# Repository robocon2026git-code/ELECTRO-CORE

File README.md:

\# GITHUB WORKFLOW GUIDE

Welcome to \*\*ROBOCON WORKSPACE\*\*

This document explains \*\*how team members should clone the repo, set up Git, and work using feature branches\*\*.

⚠️ Direct changes to `main` are NOT allowed.  

All work must be done using \*\*feature branches\*\* and merged via \*\*Pull Requests (PRs)\*\*.

---

\## 🧠 Git Basics (Quick Understanding)

\- \*\*Repository (repo)\*\* → Project stored with version control

\- \*\*main branch\*\* → Stable, reviewed code only

\- \*\*feature branch\*\* → Your personal workspace

\- \*\*commit\*\* → A saved snapshot of changes

\- \*\*origin\*\* → Remote GitHub repository

\- \*\*Pull Request (PR)\*\* → Request to merge code into `main`

---

\## One-Time Setup (Required on Every New PC)

Run these commands \*\*once\*\* after installing Git:

```bash

git config --global user.name "Your Name"

git config --global user.email "your-email@example.com"

git config --global init.defaultBranch main

\## To verify configuration

git config --global --list

**## Cloning and work steps starts from here:**

!!!!IMPORTANT ONE TIME SETTING AFTER INSTALLED GIT:

git clone https://github.com/robocon2026git-code/ELECTRICAL-AND-EMBEDDED.git

# \## REGULAR WORK PROCEDURE

1)cd ELECTRO-CORE

2)git status

3)git checkout main					//This line says go to main branch

4)git pull origin main					//Important step otherwise you might miss some files that was updated recently

5)git checkout -b feature/short-description		//Creating your local workspace

    ex:

        git checkout -b feature/pneumatic\_actuation

	git checkout -b feature/arduino-motor

	git checkout -b feature/i2c-driver

After work done run this command once

6)git status

\## THE FOLLOWING STEPS ARE AFTER COMPLETION OF YOUR WORK

\*\* THIS THREE COMMENTS WE WILL USE FREQUENTLY

7)git add .

8)git commit -m "Added new functionality to drive train"

Run this command only when your first push after creation of your feature branch

9) a_)git push -u origin feature/your-branch-name

from next push onwards you can just type

   b_)git push

For local space

10) a_)git branch -d feature/your-branch-name		//Run this comment only after code is merged. This will delete your branch

For remote space

    b_)git push origin --delete feature/your-branch-name

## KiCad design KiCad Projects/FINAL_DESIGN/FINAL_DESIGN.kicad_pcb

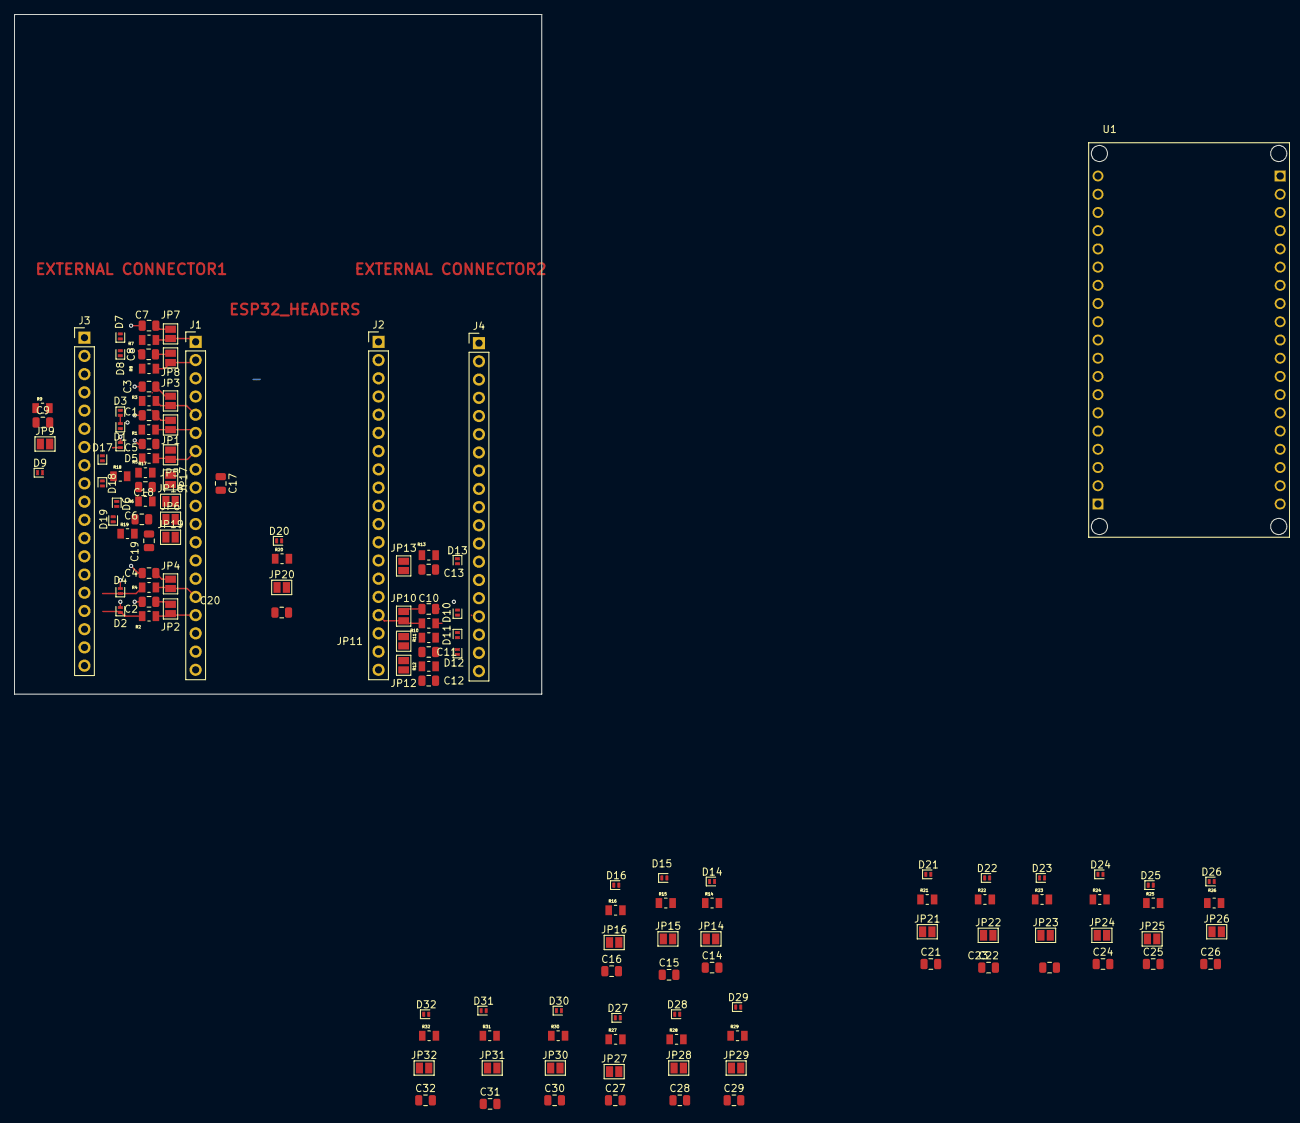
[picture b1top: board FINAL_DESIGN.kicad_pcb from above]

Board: 2 copper layers, 73.5 x 94.8 mm, 133 parts (0 on the bottom side), 100 nets.

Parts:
C1, C2, C3, C4, C5, C6, C7, C8, C9, C10, C11, C12, C13, C14, C15, C16, C17, C18, C19, C20, C21, C22, C23, C24, C25, C26, C27, C28, C29, C30, C31, C32: 100nf; C_0805_2012Metric
D1, D2, D3, D4, D5, D6, D7, D8, D9, D10, D11, D12, D13, D14, D15, D16, D17, D18, D19, D20, D21, D22, D23, D24, D25, D26, D27, D28, D29, D30, D31, D32: D_Zener; D_SOD-882
J1, J2, J3, J4: Conn_01x19_Socket; PinHeader_1x19_P2.54mm_Vertical
JP1, JP2, JP3, JP4, JP5, JP6, JP7, JP8, JP9, JP10, JP11, JP12, JP13, JP14, JP15, JP16, JP17, JP18, JP19, JP20, JP21, JP22, JP23, JP24, JP25, JP26, JP27, JP28, JP29, JP30, JP31, JP32: SolderJumper_2_Open; SolderJumper-2_P1.3mm_Open_Pad1.0x1.5mm
R1, R2, R3, R4, R5, R6, R7, R8, R9, R10, R11, R12, R13, R14, R15, R16, R17, R18, R19, R20, R21, R22, R23, R24, R25, R26, R27, R28, R29, R30, R31, R32: 150; RESC2012X60N
U1: ESP32_NODEMCU; MODULE_ESP32_NODEMCU

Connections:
+3V3: J2.1, J4.1
/CLK: D7.1 (K), J3.1, R7.1
/CMD: D12.1 (K), J4.18, R12.1
/EN: J2.2, J4.2
/IO16: JP17.2 (B), R17.2
/IO_0: J1.6, JP1.2 (B), R1.2
/IO_1: J1.16, JP2.2 (B), R2.2
/IO_2: J1.5, JP3.2 (B), R3.2
/IO_3: J1.15, JP4.2 (B), R4.2
/IO_4: J1.7, JP5.2 (B), R5.2
/IO_5: J1.10, JP6.2 (B), R6.2
/IO_6: J1.1, JP7.2 (B), R7.2
/IO_7: J1.2, JP8.2 (B), R8.2
/IO_8: J1.3, JP9.2 (B), R9.2
/IO_9: J2.16, JP10.2 (B), R10.2
/IO_10: J2.17, JP11.2 (B), R11.2
/IO_11: J2.18, JP12.2 (B), R12.2
/IO_12: J2.13, JP13.2 (B), R13.2
/IO_13: J2.15, JP14.2 (B), R14.2
/IO_14: J2.12, JP15.2 (B), R15.2
/IO_15: J1.4, JP16.2 (B), R16.2
/IO_17: J1.9, JP18.2 (B), R18.2
/IO_18: J1.11, JP19.2 (B), R19.2
/IO_19: J1.12, JP20.2 (B), R20.2
/IO_21: J1.14, JP21.2 (B), R21.2
/IO_23: J1.18, JP23.2 (B), R23.2
/IO_25: J2.9, JP24.2 (B), R24.2
/IO_26: J2.10, JP25.2 (B), R25.2
/IO_27: J2.11, JP26.2 (B), R26.2
/IO_32: J2.7, JP27.2 (B), R27.2
/IO_33: J2.8, JP28.2 (B), R28.2
/IO_34: J2.5, JP29.2 (B), R29.2
/IO_35: J2.6, JP30.2 (B), R30.2
/IO_36: J2.3, JP31.2 (B), R31.2
/IO_39: J2.4, JP32.2 (B), R32.2
/IO­_22: JP22.2 (B), R22.2
/I/O_0: D1.1 (K), J3.6, R1.1
/I/O_2: D3.1 (K), J3.5, R3.1
/I/O_4: D5.1 (K), J3.7, R5.1
/I/O_5: D6.1 (K), J3.10, R6.1
/I/O_12: D13.1 (K), J4.13, R13.1
/I/O_13: D14.1 (K), J4.15, R14.1
/I/O_14: D15.1 (K), J4.12, R15.1
/I/O_15: D16.1 (K), J3.4, R16.1
/I/O_16: D17.1 (K), J3.8, R17.1
/I/O_17: D18.1 (K), J3.9, R18.1
/I/O_18: D19.1 (K), J3.11, R19.1
/I/O_19: D20.1 (K), J3.12, R20.1
/I/O_21: D21.1 (K), J3.14, R21.1
/I/O_22: D22.1 (K), J3.17, R22.1
/I/O_23: D23.1 (K), J3.18, R23.1
/I/O_25: D24.1 (K), J4.9, R24.1
/I/O_26: D25.1 (K), J4.10, R25.1
/I/O_27: D26.1 (K), J4.11, R26.1
/I/O_32: D27.1 (K), J4.7, R27.1
/I/O_33: D28.1 (K), J4.8, R28.1
/I/O_34: D29.1 (K), J4.5, R29.1
/I/O_35: D30.1 (K), J4.6, R30.1
/RXD: D4.1 (K), J3.15, R4.1
/SD0: D8.1 (K), J3.2, R8.1
/SD1: D9.1 (K), J3.3, R9.1
/SD2: D10.1 (K), J4.16, R10.1
/SD3: D11.1 (K), J4.17, R11.1
/SN: D32.1 (K), J4.4, R32.1
/SP: D31.1 (K), J4.3, R31.1
/TXD: D2.1 (K), J3.16, R2.1
GND: C1.2, C2.2, C3.2, C4.2, C5.2, C6.2, C7.2, C8.2, C9.2, C10.2, C11.2, C12.2, C13.2, C14.2, C15.2, C16.2, C17.2, C18.2, C19.2, C20.2, C21.2, C22.2, C23.2, C24.2, C25.2, C26.2, C27.2, C28.2, C29.2, C30.2, C31.2, C32.2, D1.2 (A), D2.2 (A), D3.2 (A), D4.2 (A), D5.2 (A), D6.2 (A), D7.2 (A), D8.2 (A), D9.2 (A), D10.2 (A), D11.2 (A), D12.2 (A), D13.2 (A), D14.2 (A), D15.2 (A), D16.2 (A), D17.2 (A), D18.2 (A), D19.2 (A), D20.2 (A), D21.2 (A), D22.2 (A), D23.2 (A), D24.2 (A), D25.2 (A), D26.2 (A), D27.2 (A), D28.2 (A), D29.2 (A), D30.2 (A), D31.2 (A), D32.2 (A), J1.13, J1.19, J2.14, J3.13, J3.19, J4.14
unnamed: C1.1, JP1.1 (A)
unnamed: C2.1, JP2.1 (A)
unnamed: C3.1, JP3.1 (A)
unnamed: C4.1, JP4.1 (A)
unnamed: C5.1, JP5.1 (A)
unnamed: C6.1, JP6.1 (A)
unnamed: C7.1, JP7.1 (A)
unnamed: C8.1, JP8.1 (A)
unnamed: C9.1, JP9.1 (A)
unnamed: C10.1, JP10.1 (A)
unnamed: C11.1, JP11.1 (A)
unnamed: C12.1, JP12.1 (A)
unnamed: C13.1, JP13.1 (A)
unnamed: C14.1, JP14.1 (A)
unnamed: C15.1, JP15.1 (A)
unnamed: C16.1, JP16.1 (A)
unnamed: C17.1, JP17.1 (A)
unnamed: C18.1, JP18.1 (A)
unnamed: C19.1, JP19.1 (A)
unnamed: C20.1, JP20.1 (A)
unnamed: C21.1, JP21.1 (A)
unnamed: C22.1, JP22.1 (A)
unnamed: C23.1, JP23.1 (A)
unnamed: C24.1, JP24.1 (A)
unnamed: C25.1, JP25.1 (A)
unnamed: C26.1, JP26.1 (A)
unnamed: C27.1, JP27.1 (A)
unnamed: C28.1, JP28.1 (A)
unnamed: C29.1, JP29.1 (A)
unnamed: C30.1, JP30.1 (A)
unnamed: C31.1, JP31.1 (A)
unnamed: C32.1, JP32.1 (A)
VIN 5V: J2.19, J4.19

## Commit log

2026-01-05 Added working STM32 codes to Git hub, Integration_code and locomotion code
2026-01-05 Arduino_IDE_Code --> ESP32_Code Added
2026-01-08 Delete text1.txt
    Not required
2026-01-08 Edited README.md
2026-01-09 testing
2026-01-10 Added ESP32 protection sheild circuit
2026-01-11 Deleted some files to make workspace clean
2026-01-12 Design process
2026-01-12 Update README.md
    Website correction
2026-01-13 Working
2026-01-19 pcb design
2026-01-23 Design
2026-01-24 new code
2026-01-26 locomotion.c modified for bldc and esc
